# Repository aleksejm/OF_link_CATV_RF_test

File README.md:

# OF_link_CATV_RF_test
Optical fiber link and CATV RF test device

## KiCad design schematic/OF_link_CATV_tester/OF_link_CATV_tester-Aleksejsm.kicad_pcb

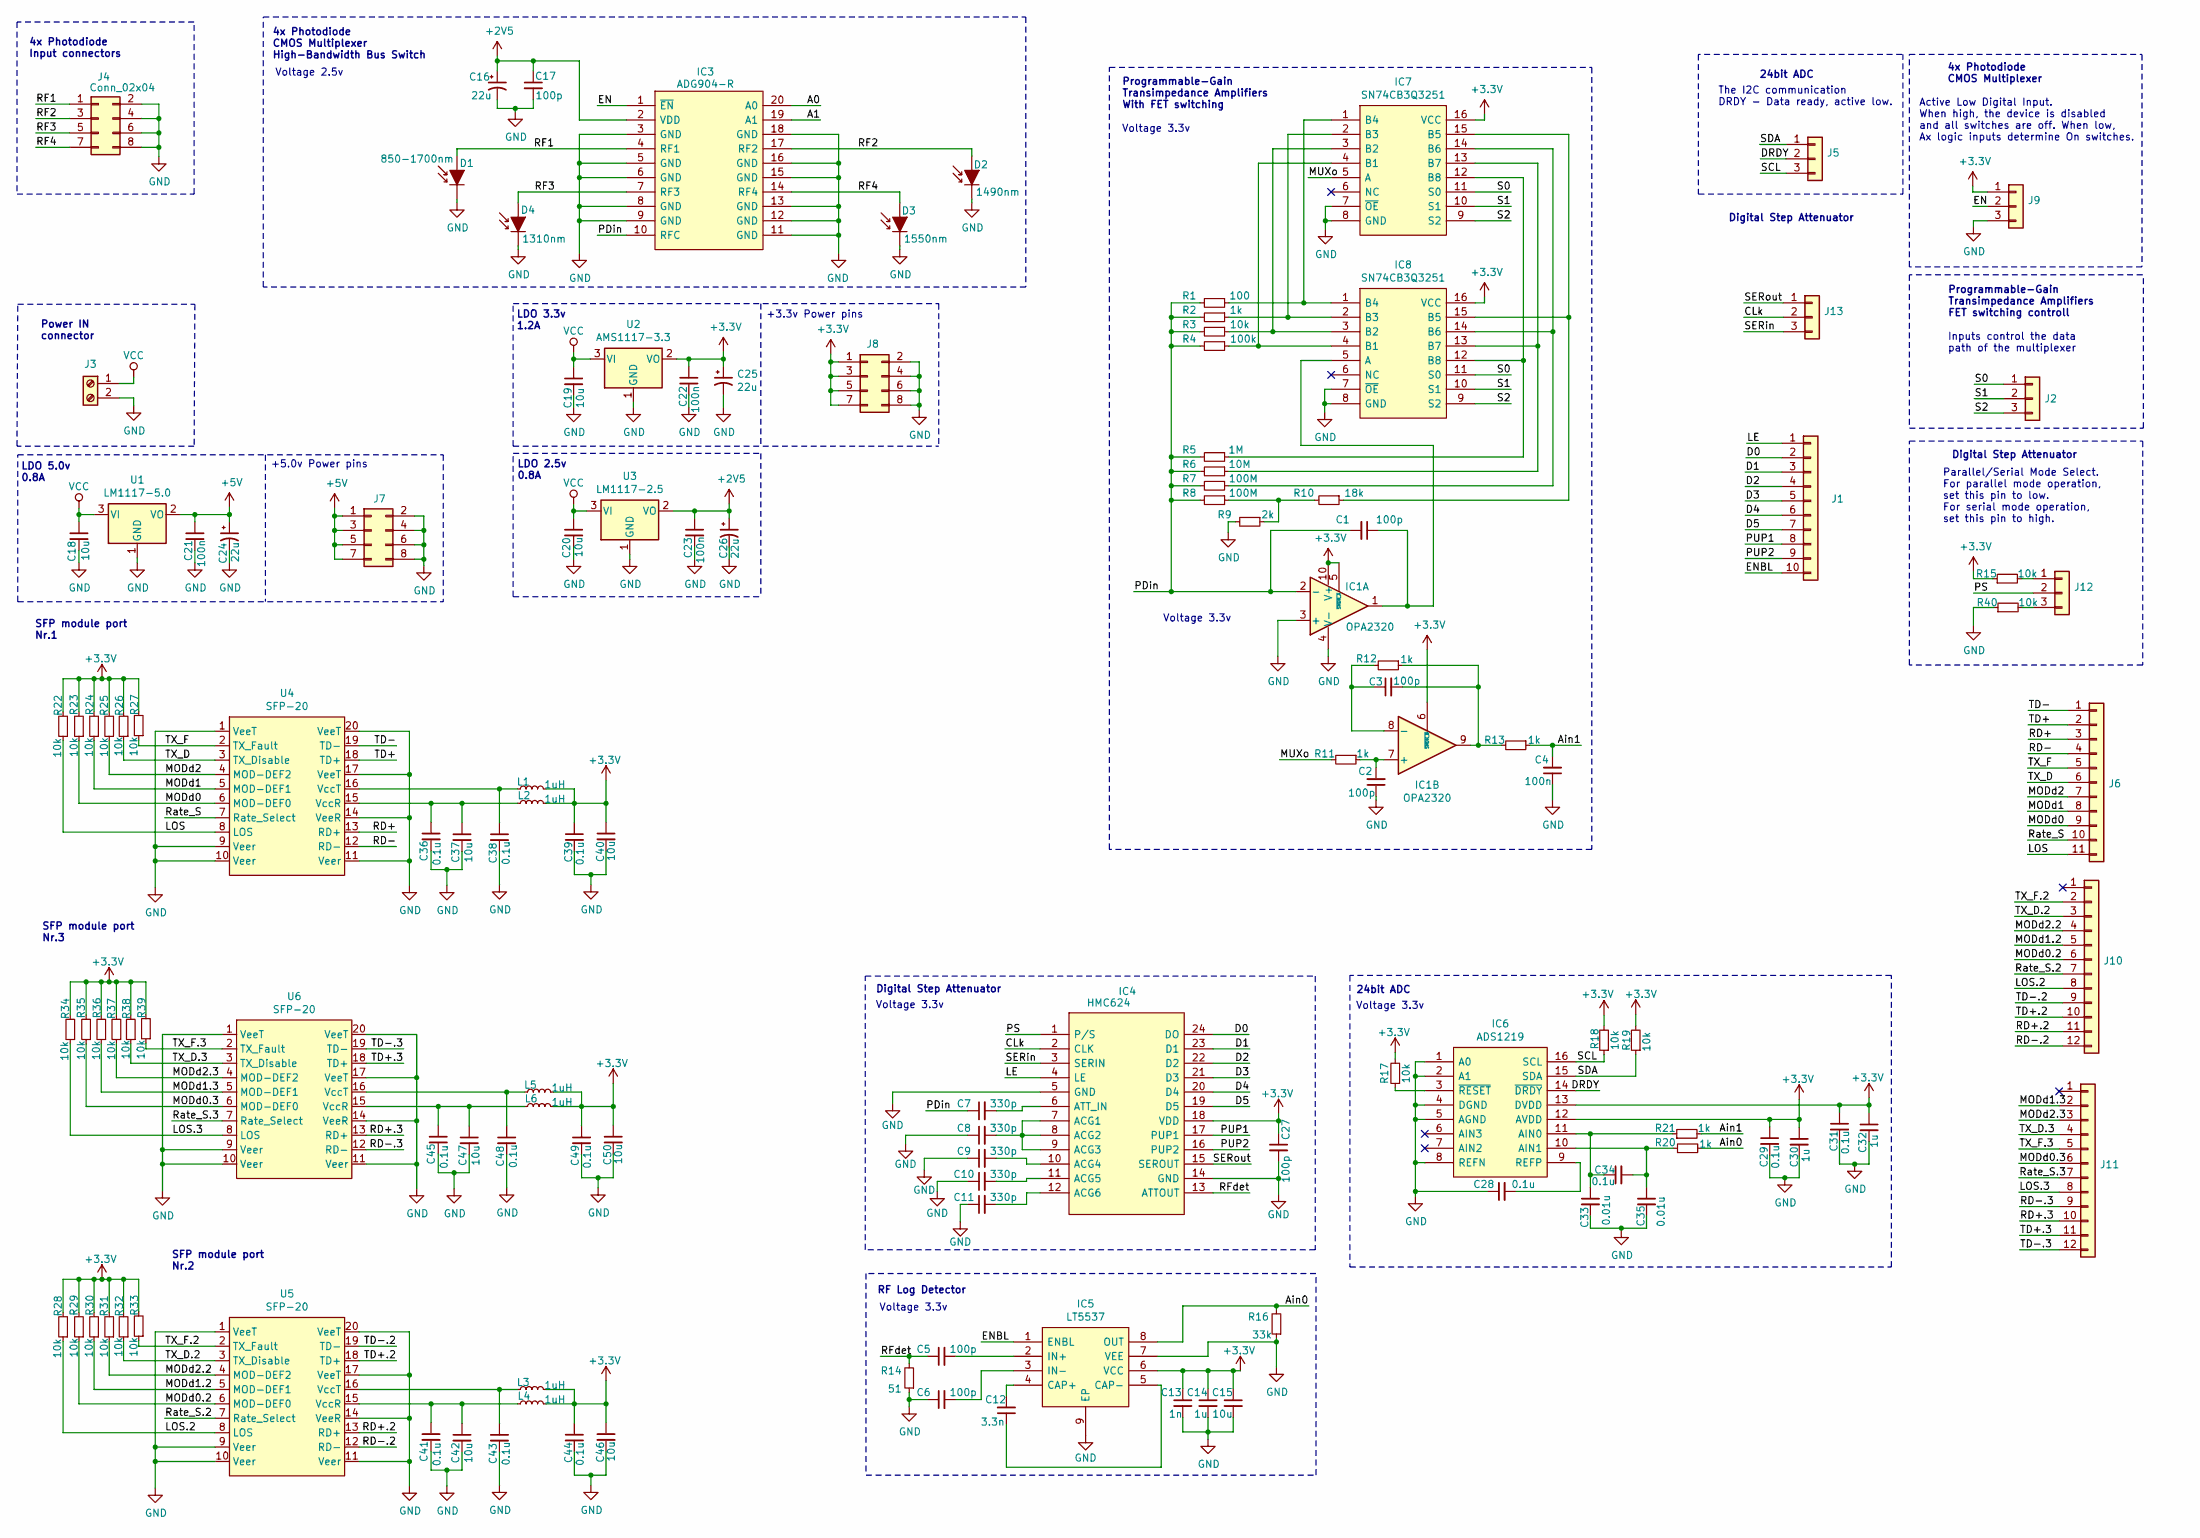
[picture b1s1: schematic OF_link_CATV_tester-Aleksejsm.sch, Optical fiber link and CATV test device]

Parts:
C1, C2, C3, C6: 100p; C_0603_1608Metric
C4: 100n; C_0603_1608Metric
C5, C17, C27: 100p; C_0603_1608Metric; Tolerance 5%; Voltage 50V
C7, C8, C9, C10, C11: 330p; C_0603_1608Metric
C12: 3.3n; C_0603_1608Metric
C13: 1n; C_0603_1608Metric
C14: 1u; C_0603_1608Metric
C15: 10u; C_0603_1608Metric
C16, C24, C25, C26: 22u; CP_EIA-3216-18_Kemet-A; Tolerance 20%; Voltage 6.3V
C18, C19, C20: 10u; C_0805_2012Metric
C21, C22, C23: 100n; C_0805_2012Metric; Tolerance 5%; Voltage 50V
C28, C29, C31, C34, C36, C38, C39, C41, C43, C44, C45, C48, C49: 0.1u; C_0603_1608Metric; Tolerance 10%; Voltage 10V
C30, C32: 1u; C_0603_1608Metric; Tolerance 10%; Voltage 10V
C33, C35: 0.01u; C_0603_1608Metric; Tolerance 10%; Voltage 10V
C37, C40, C42, C46, C47, C50: 10u; C_0603_1608Metric; Tolerance 10%; Voltage 10V
D1: 850-1700nm
D2: 1490nm
D3: 1550nm
D4: 1310nm
IC1: OPA2320; VSSOP-10_3x3mm_P0.5mm; Manufacturer_Part_Number OPA2320SAIDGST; Mouser Part Number 595-OPA2320SAIDGST
IC3: ADG904-R; TSSOP-20_4.4x6.5mm_P0.65mm; Manufacturer_Part_Number ADG904BRUZ-R; Mouser Part Number 584-ADG904BRUZ-R
IC4: HMC624; WQFN-24-1EP_4x4mm_P0.5mm_EP2.7x2.7mm; Manufacturer_Part_Number HMC624ALP4E; Mouser Part Number 584-HMC624ALP4E
IC5: LT5537; DFN-8-1EP_2x3mm_P0.5mm_EP0.61x2.2mm; Manufacturer_Part_Number LT5537EDDB#TRMPBF
IC6: ADS1219; TSSOP-16_4.4x5mm_P0.65mm; Manufacturer_Part_Number ADS1219IPWR; Mouser Part Number 595-ADS1219IPWR
IC7, IC8: SN74CB3Q3251; SSOP-16_4.4x5.2mm_P0.65mm; Manufacturer_Part_Number SN74CB3Q3251DGVR
J1: Conn_01x10; PinHeader_1x10_P2.54mm_Vertical
J2, J5, J9, J12, J13: Conn_01x03; PinHeader_1x03_P2.54mm_Vertical
J3: Screw_Terminal_01x02; TerminalBlock_4Ucon_1x02_P3.50mm_Horizontal
J4, J7, J8: Conn_02x04; PinHeader_2x04_P2.54mm_Vertical
J6: Conn_01x11; PinHeader_1x11_P2.54mm_Vertical
J10, J11: Conn_01x12; PinHeader_1x12_P2.54mm_Vertical
L1, L2, L3, L4, L5, L6: 1uH; L_0603_1608Metric
R1: 100; R_0805_2012Metric
R2, R11, R12, R13, R20, R21: 1k; R_0805_2012Metric
R3, R15, R17, R18, R19, R22, R23, R24, R25, R26, R27, R28, R29, R30, R31, R32, R33, R34, R35, R36, R37, R38, R39, R40: 10k; R_0805_2012Metric
R4: 100k; R_0805_2012Metric
R5: 1M; R_0805_2012Metric
R6: 10M; R_0805_2012Metric
R7, R8: 100M; R_0805_2012Metric
R9: 2k; R_0805_2012Metric
R10: 18k; R_0805_2012Metric
R14: 51; R_0805_2012Metric
R16: 33k; R_0805_2012Metric
U1: LM1117-5.0; SOT-223
U2: AMS1117-3.3; SOT-223-3_TabPin2
U3: LM1117-2.5; SOT-223
U4, U5, U6: SFP-20

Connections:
+2V5: C16.1, C17.1, C23.1, C26.1, IC3.2 (VDD), U3.2 (VO)
+3V3: C13.1, C14.1, C15.1, C22.1, C25.1, C27.1, C29.1, C30.1, C31.1, C32.1, C39.1, C40.1, C44.1, C46.1, C49.1, C50.1, IC1.5 (~SHDN_A), IC1.6 (~SHDN_B), IC1.10 (V+), IC4.18 (VDD), IC5.6 (VCC), IC6.12 (AVDD), IC6.13 (DVDD), IC7.16 (VCC), IC8.16 (VCC), J8.1, J8.3, J8.5, J8.7, J9.1, L1.2, L2.2, L3.2, L4.2, L5.2, L6.2, R15.1, R17.2, R18.2, R19.2, R22.2, R23.2, R24.2, R25.2, R26.2, R27.2, R28.2, R29.2, R30.2, R31.2, R32.2, R33.2, R34.2, R35.2, R36.2, R37.2, R38.2, R39.2, U2.2 (VO)
+5V: C21.1, C24.1, J7.1, J7.3, J7.5, J7.7, U1.2 (VO)
/A0: IC3.20 (A0)
/A1: IC3.19 (A1)
/Ain0: IC5.8 (OUT), R16.2, R20.2
/Ain1: C4.2, R13.1, R21.2
/CLk: IC4.2 (CLK), J13.2
/D0: IC4.24 (DO), J1.2
/D1: IC4.23 (D1), J1.3
/D2: IC4.22 (D2), J1.4
/D3: IC4.21 (D3), J1.5
/D4: IC4.20 (D4), J1.6
/D5: IC4.19 (D5), J1.7
/DRDY: IC6.14 (~DRDY), J5.2
/EN: IC3.1 (~EN), J9.2
/ENBL: IC5.1 (ENBL), J1.10
/LE: IC4.4 (LE), J1.1
/LOS: J6.11, R22.1, U4.8 (LOS)
/LOS.2: J10.8, R28.1, U5.8 (LOS)
/LOS.3: J11.8, R34.1, U6.8 (LOS)
/MODd0: J6.9, R23.1, U4.6 (MOD-DEF0)
/MODd0.2: J10.6, R29.1, U5.6 (MOD-DEF0)
/MODd0.3: J11.6, R35.1, U6.6 (MOD-DEF0)
/MODd1: J6.8, R24.1, U4.5 (MOD-DEF1)
/MODd1.2: J10.5, R30.1, U5.5 (MOD-DEF1)
/MODd1.3: J11.2, R36.1, U6.5 (MOD-DEF1)
/MODd2: J6.7, R25.1, U4.4 (MOD-DEF2)
/MODd2.2: J10.4, R31.1, U5.4 (MOD-DEF2)
/MODd2.3: J11.3, R37.1, U6.4 (MOD-DEF2)
/MUXo: IC7.5 (A), R11.2
/PDin: C1.2, C7.1, IC1.2 (-), IC3.10 (RFC), R1.2, R2.2, R3.2, R4.2, R5.2, R6.2, R7.2, R8.2
/PS: IC4.1 (P/S), J12.2
/PUP1: IC4.17 (PUP1), J1.8
/PUP2: IC4.16 (PUP2), J1.9
/RD+: J6.3, U4.13 (RD+)
/RD+.2: J10.11, U5.13 (RD+)
/RD+.3: J11.10, U6.13 (RD+)
/RD-: J6.4, U4.12 (RD-)
/RD-.2: J10.12, U5.12 (RD-)
/RD-.3: J11.9, U6.12 (RD-)
/RF1: D1.2 (A), IC3.4 (RF1), J4.1
/RF2: D2.2 (A), IC3.17 (RF2), J4.3
/RF3: D4.2 (A), IC3.7 (RF3), J4.5
/RF4: D3.2 (A), IC3.14 (RF4), J4.7
/RFdet: C5.1, IC4.13 (ATTOUT), R14.2
/Rate_S: J6.10, U4.7 (Rate_Select)
/Rate_S.2: J10.7, U5.7 (Rate_Select)
/Rate_S.3: J11.7, U6.7 (Rate_Select)
/S0: IC7.11 (S0), IC8.11 (S0), J2.1
/S1: IC7.10 (S1), IC8.10 (S1), J2.2
/S2: IC7.9 (S2), IC8.9 (S2), J2.3
/SCL: IC6.16 (SCL), J5.3, R18.1
/SDA: IC6.15 (SDA), J5.1, R19.1
/SERin: IC4.3 (SERIN), J13.3
/SERout: IC4.15 (SEROUT), J13.1
/TD+: J6.2, U4.18 (TD+)
/TD+.2: J10.10, U5.18 (TD+)
/TD+.3: J11.11, U6.18 (TD+)
/TD-: J6.1, U4.19 (TD-)
/TD-.2: J10.9, U5.19 (TD-)
/TD-.3: J11.12, U6.19 (TD-)
/TX_D: J6.6, R26.1, U4.3 (TX_Disable)
/TX_D.2: J10.3, R32.1, U5.3 (TX_Disable)
/TX_D.3: J11.4, R38.1, U6.3 (TX_Disable)
/TX_F: J6.5, R27.1, U4.2 (TX_Fault)
/TX_F.2: J10.2, R33.1, U5.2 (TX_Fault)
/TX_F.3: J11.5, R39.1, U6.2 (TX_Fault)
GND: C2.1, C4.1, C6.1, C8.1, C9.1, C10.1, C11.1, C13.2, C14.2, C15.2, C16.2, C17.2, C18.2, C19.2, C20.2, C21.2, C22.2, C23.2, C24.2, C25.2, C26.2, C27.2, C28.1, C29.2, C30.2, C31.2, C32.2, C33.2, C35.2, C36.2, C37.2, C38.2, C39.2, C40.2, C41.2, C42.2, C43.2, C44.2, C45.2, C46.2, C47.2, C48.2, C49.2, C50.2, D1.1 (K), D2.1 (K), D3.1 (K), D4.1 (K), IC1.3 (+), IC1.4 (V-), IC1.11 (V-), IC3.3 (GND), IC3.5 (GND), IC3.6 (GND), IC3.8 (GND), IC3.9 (GND), IC3.11 (GND), IC3.12 (GND), IC3.13 (GND), IC3.15 (GND), IC3.16 (GND), IC3.18 (GND), IC4.5 (GND), IC4.14 (GND), IC5.7 (VEE), IC5.9 (EP), IC6.1 (A0), IC6.2 (A1), IC6.4 (DGND), IC6.5 (AGND), IC6.8 (REFN), IC7.7 (~OE), IC7.8 (GND), IC8.7 (~OE), IC8.8 (GND), J3.2, J4.2, J4.4, J4.6, J4.8, J7.2, J7.4, J7.6, J7.8, J8.2, J8.4, J8.6, J8.8, J9.3, R9.2, R14.1, R16.1, R40.1, U1.1 (GND), U2.1 (GND), U3.1 (GND), U4.1 (VeeT), U4.9 (Veer), U4.10 (Veer), U4.11 (Veer), U4.14 (VeeR), U4.17 (VeeT), U4.20 (VeeT), U5.1 (VeeT), U5.9 (Veer), U5.10 (Veer), U5.11 (Veer), U5.14 (VeeR), U5.17 (VeeT), U5.20 (VeeT), U6.1 (VeeT), U6.9 (Veer), U6.10 (Veer), U6.11 (Veer), U6.14 (VeeR), U6.17 (VeeT), U6.20 (VeeT)
unnamed: C1.1, IC1.1, IC8.5 (A)
unnamed: C2.2, IC1.7 (+), R11.1
unnamed: C3.1, IC1.8 (-), R12.2
unnamed: C3.2, IC1.9, R12.1, R13.2
unnamed: C5.2, IC5.2 (IN+)
unnamed: C6.2, IC5.3 (IN-)
unnamed: C7.2, IC4.6 (ATT_IN)
unnamed: C8.2, IC4.7 (ACG1), IC4.8 (ACG2), IC4.9 (ACG3)
unnamed: C9.2, IC4.10 (ACG4)
unnamed: C10.2, IC4.11 (ACG5)
unnamed: C11.2, IC4.12 (ACG6)
unnamed: C12.1, IC5.5 (CAP-)
unnamed: C12.2, IC5.4 (CAP+)
unnamed: C28.2, IC6.9 (REFP)
unnamed: C33.1, C34.1, IC6.11 (AIN0), R21.1
unnamed: C34.2, C35.1, IC6.10 (AIN1), R20.1
unnamed: C36.1, C37.1, L2.1, U4.15 (VccR)
unnamed: C38.1, L1.1, U4.16 (VccT)
unnamed: C41.1, C42.1, L4.1, U5.15 (VccR)
unnamed: C43.1, L3.1, U5.16 (VccT)
unnamed: C45.1, C47.1, L6.1, U6.15 (VccR)
unnamed: C48.1, L5.1, U6.16 (VccT)
unnamed: IC6.3 (~RESET), R17.1
unnamed: IC7.1 (B4), IC8.1 (B4), R1.1
unnamed: IC7.2 (B3), IC8.2 (B3), R2.1
unnamed: IC7.3 (B2), IC8.3 (B2), R3.1
unnamed: IC7.4 (B1), IC8.4 (B1), R4.1
unnamed: IC7.12 (B8), IC8.12 (B8), R5.1
unnamed: IC7.13 (B7), IC8.13 (B7), R6.1
unnamed: IC7.14 (B6), IC8.14 (B6), R7.1
unnamed: IC7.15 (B5), IC8.15 (B5), R10.1
unnamed: J12.1, R15.2
unnamed: J12.3, R40.2
unnamed: R8.1, R9.1, R10.2
VCC: C18.1, C19.1, C20.1, J3.1, U1.3 (VI), U2.3 (VI), U3.3 (VI)

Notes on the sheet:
Digital Step Attenuator
RF Log Detector
4x Photodiode CMOS Multiplexer High-Bandwidth Bus Switch
24bit ADC
Voltage 2.5v
Voltage 3.3v
LDO 2.5v 0.8A
LDO 3.3v 1.2A
LDO 5.0v 0.8A
Programmable-Gain Transimpedance Amplifiers With FET switching
4x Photodiode Input connectors
Power IN connector
+3.3v Power pins
+5.0v Power pins
Active Low Digital Input. When high, the device is disabled and all switches are off. When low, Ax logic inputs determine On switches.
4x Photodiode CMOS Multiplexer
Programmable-Gain Transimpedance Amplifiers FET switching controll
Inputs control the data path of the multiplexer
SFP module port Nr.1
SFP module port Nr.3
SFP module port Nr.2
Parallel/Serial Mode Select. For parallel mode operation, set this pin to low. For serial mode operation, set this pin to high.
The I2C communication DRDY - Data ready, active low.

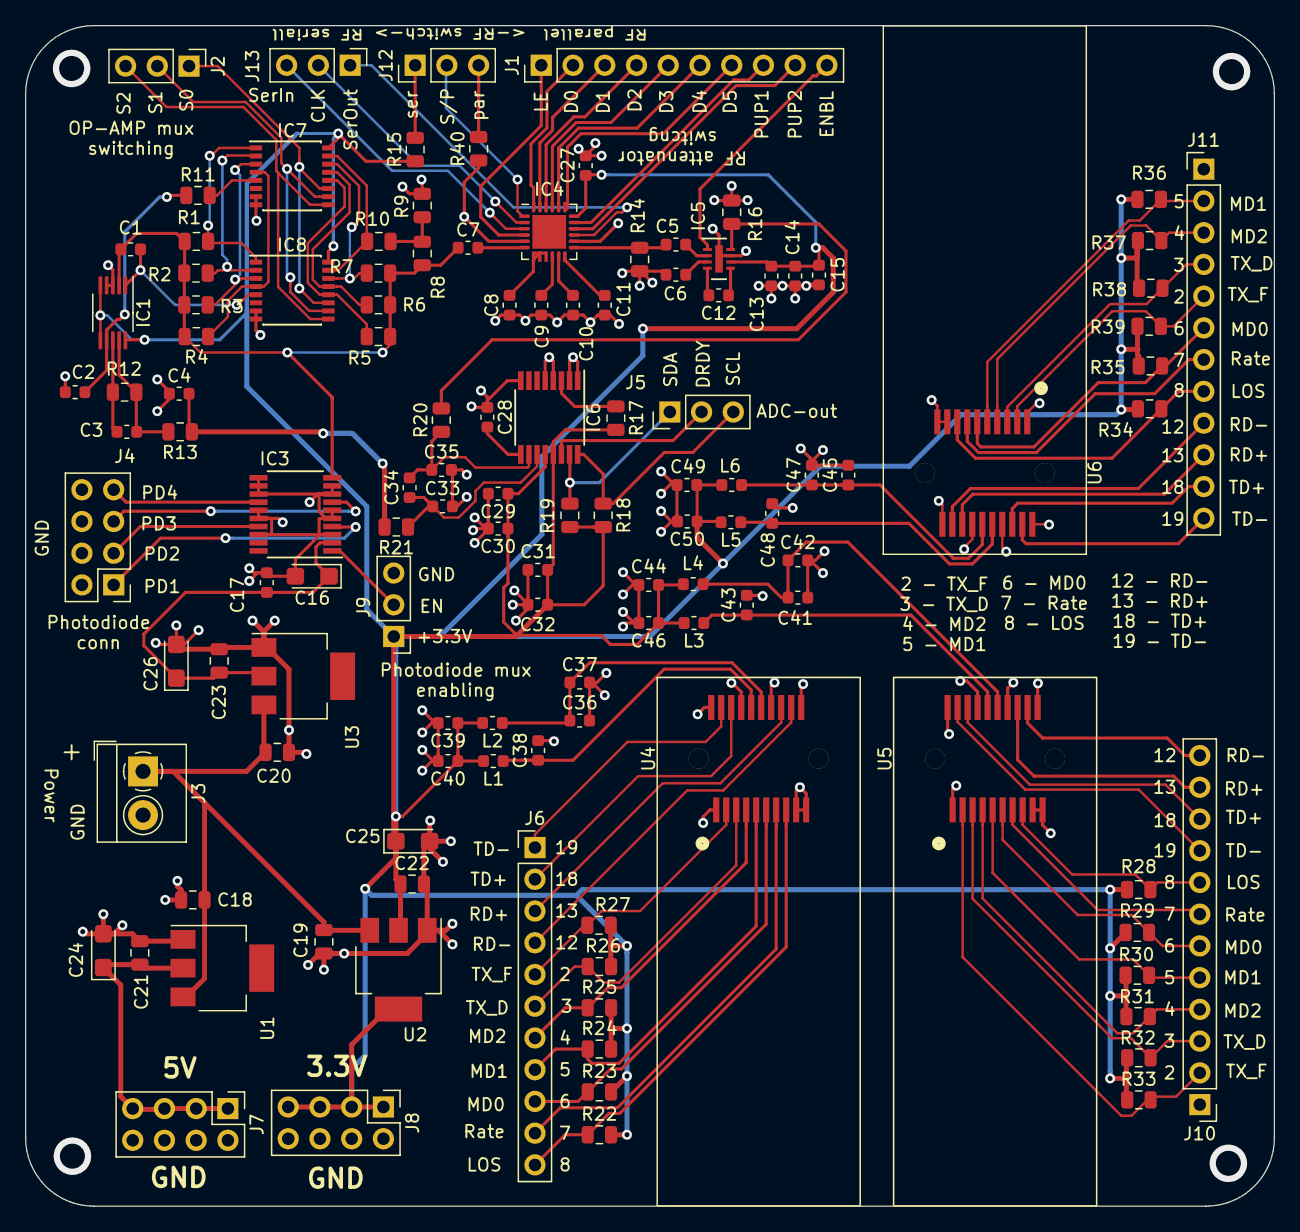
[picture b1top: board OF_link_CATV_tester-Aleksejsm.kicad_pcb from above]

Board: 2 copper layers, 99.9 x 94.5 mm, 122 parts (0 on the bottom side), 102 nets.

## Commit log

2019-05-13 Updated schematic and PCB
    Changed error footprints in PCB
